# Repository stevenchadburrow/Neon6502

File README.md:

# Neon6502

<b>Compact 6502 build using 74' logic chips.</b>

The idea with this project is to make a cheap 4" x 4" PCB that can fit most of the functionality of my original <a href="https://github.com/stevenchadburrow/AcolyteComputer">Acolyte Computer</a>.  The purpose is to play games such as Tetris and Space Invaders clones that I will program in 6502 assembly.  I also made a simulator program is to help speed up development time and lessen the amount of Flash ROM burns.<br>

I'm doing this in order to wait for the <a href="https://www.microchip.com/en-us/product/PIC32CZ8110CA80144">PIC32CZ8110CA80144</a> microcontroller to come out in the LQFP-144 package (promised Q4 of 2025!).  Once that is out, I will get back to projects similar to my <a href="https://github.com/stevenchadburrow/AcolyteHandheld">Acolyte Handheld<a>.<br>

<b>Specs:</b><br>
- W65C02 running at 3.14 MHz<br>
- 32 KB of RAM (30 KB of which is Video RAM)<br>
- 32 KB of ROM (4x switchable banks)<br>
- 8x Built-in Buttons<br>
- VGA Output of 320x240 in 4-colors<br>
- Uses only 74' logic chips and the Flash ROM to generate the video signal!<br>
- USB-B to power device<br>
- No VIA, no UART, no keyboard, no audio, no external memory<br>

<b>Memory Map:</b><br>
- $0000 - $07FF = RAM<br>
- $0800 - $7FFF = Video RAM<br>
- $8000 - $FFFF = ROM<br>

<b>History:</b><br>
As this is a revisiting of previous projects and skills, I feel the need to try to catalog my progress up to this point.  Below is a timeline of projects completed with a few details.<br>
- Aug 2021: After the quarantine, I went back to work at the school physically.  I never went upstairs into my office but stayed in my classroom with a Linux computer to occupy my time.  I started researching how to make a water-based calculator, but found electricity to be far better.  I researched about 74' logic chips and eventually reached out to Garth who redirected me to the 6502.org Forum <a href="http://forum.6502.org/">here</a>.
- Oct 2021: This marks the very beginning of the journey, my first 6502 build, called "V1" by Bill (plasmo).  Made on perf-board, each wire hand-soldered.  I had crossed A4 and A11 on the RAM, Bill found this and fixed it for me.  It had only a couple of buttons and a 16x2 LCD.
- Nov 2021: I made a duplicate of V1 on a PCB, which I called "V2".  No bodges were required, though it wasn't very useful.  Far later I would use this as the basis for a project where Elizabeth soldered her own computer together.
- Jan 2022: I made V3 and even a V4, adding features such as PS/2 keyboard and ROM banks.  I tried to add VGA video using 74' logic chips for all sync calculations, but they were all failures.
- Mar 2022: In order to create a VGA video signal, I created my "Half a Pi" board, using a dedicated Flash ROM for video signals.  It was able to output White, Red, Cyan, and Black.  I was able to showcase it at the upcoming Math Appreciation Day 2022 <a href="http://forum.6502.org/viewtopic.php?f=1&t=7092">here</a>.
- Jul 2022: By now I had tried to replicate the "Half a Pi" with more complexity, and yet I continued to have failures.  At some point I had started calling them "Acolyte", though apparently the first versions were not operational.  The main goal was to combine both the sync signals and the program code onto a single Flash ROM.  Some were successes, even if they were complex, found <a href="http://forum.6502.org/viewtopic.php?f=4&t=7154">here</a>.
- Nov 2022: At this point I was still making mistakes and a lot of my PCBs would not work.  A revelation came to be at some point here that I could simply bodge wires to fix problems, which helped a lot.  You can find a lot of the discussion <a href="http://forum.6502.org/viewtopic.php?f=4&t=7407">here</a>.
- Jan 2023: The final culmination of the original Acolyte computers comes together <a href="https://github.com/stevenchadburrow/AcolyteComputer">here</a>.  It was named "Last Acolyte II".  It has so many bodge wires, mostly for experimenting and adding a VIA into the expansion area.  The back of that board looks like spagetti with all of the bodges!  It had Tetris, Space Invaders, BASIC, and a Monitor program.
- Apr 2023: I started designing the "Serial VGA" projects <a href="https://github.com/stevenchadburrow/SerialVGA">here</a>, which could be connected to any random 6502 computer.  After some revisions they started to work, but were not very efficient, being too slow.  I also played around with the Arduino, and created a CPLD-based shield <a href="https://github.com/stevenchadburrow/ArduinoShield">here</a>.
- Sep 2023: By now I had been working with CPLDs and learning Verilog, and created what I called "New Acolyte" <a href="https://github.com/stevenchadburrow/NewAcolyte">here</a>, which ran twice as fast and relied on the CPLD for video generation with 16 colors.  I connected a Sega Genesis controller to it, and was able to create many fun games for it, including Tetris, Space Invaders, Missile Command, Rogue, and Galaga clones.
- Dec 2023: After other failed revisions, it was time to go bigger and better, and so I developed my 'masterpiece', the "Acolyte816" <a href="https://github.com/stevenchadburrow/Acolyte816">here</a>.  It used a 65816 processor, CPLD for video generation, and a PIC16 micrcontroller for bootloading.  It did work, but was so complex that it was very hard to develop for.  Because of that, not much time was spent on it.
- Feb 2024: Enticed by the PIC16 which Garth had introduced to me, I started work on a PIC18 microcontroller based computer called "Acolyte Hand PIC'd", found <a href="https://github.com/stevenchadburrow/AcolyteHandPICd">here</a>.  It was a separation from the 6502 based computers, finally breaking away and being able to use C programming.  It still using a CPLD and external RAM for video generation.  I was able to get Tetris to run on it.  I would try another PIC18 project later that failed to work because I made it too complex.
- May 2024: I created a PIC24 microcontroller based computer called "Acolyte Hand PIC'd 24" <a href="https://github.com/stevenchadburrow/AcolyteHandPICd24">here</a>.  I was final able to break away from using the CPLD and external RAM for video generation, still yielding 16 colors.  Small additions to test USB host and device capabilities were added.  Then during Summer 2024 I created a two-player Pokemon clone for this computer, pushing the PIC24 to the very limit.
- Oct 2024: I upgraded to the PIC32 microcontroller, creating a computer called the "Acolyte Hand PIC'd 32" with absolutely stunning results <a href="https://github.com/stevenchadburrow/AcolyteHandPICd32">here</a>.  I started running it at 200 MHz, displaying 256 colors.  I bodged in better audio capabilities using an R2R DAC and was able to play video/audio streams.
- Dec 2024: After trying to port an NES emulator to the PIC32 board, and failing to reach the needed speed, I found the Peanut-GB Emulator by Mahyar <a href="https://github.com/deltabeard/Peanut-GB">here</a>.  It ran Gameboy games at full speed.  I quickly made a second revision of the PIC32 board with 64K color capability and 2x 8-bit R2R DACs.
- Jan 2025: Wanting to create a handheld device of some kind, I created "Mon Catcher" using a PIC24 and a small LCD.  It was going to be a dedicated device that would act similar to Pokemon GO, using sensors to detect movement.  It worked, but the sensors were not great and I got bored of it quickly. ( No links provided. )
- Feb 2025: I started work on what would later be called "PICnes" <a href="https://github.com/stevenchadburrow/PICnes">here</a>.  By April 2025 it would have all of the popular NES mappers including MMC3.
- Jun 2025: My dream forever has been to have a 'switchable' platform, and so I finally created the "Acolyte Handheld" <a href="https://github.com/stevenchadburrow/AcolyteHandheld">here</a>.  Capable of switching between VGA and LCD outputs, and being overclocked to 300 MHz, it was able to run nearly all NES games at full speed.  Along with Peanut-GB, I added TotalSMS <a href="https://github.com/ITotalJustice/TotalSMS">here</a>, for Sega Master System and Game Gear games.  Over Summer 2025 it was finalized.
- Aug 2025: In an attempt to shrink the Acolyte Handheld down, I created what I called the "Second Handheld", which would be my 'masterpiece' with the PIC32.  Unfortunately, I was not able to overclock it to 300 MHz, and many of the complex features such as external Flash ROM I had added were not working.  It ultimately ended a failure, however beautiful it was.  It seems that my 'masterpieces' always end in failure? ( No links provided. )
- Sep 2025: Seeking to make the next project better than the PIC32, I started the "RPi02W-Emulators" project <a href="https://github.com/stevenchadburrow/RPi02W-Emulators">here</a>.  Using a Raspberry Pi Zero 2W, I was able to make it 'switchable' between and LCD screen and HDMI output.  Programming in Linux was very enjoyable, though ultimately this project also proved to be a failure.  It ran NES and GB games easily enough, but Gameboy Advance games were still too slow.  The screen would have a tearing effect and the audio was scratchy, mainly because I decided to user /dev/fb0 and /dev/dsp for all of my video and audio needs.  The Linux overhead just didn't make it work as well as I had wanted.  It does run Freedoom, but only on HDMI.
- Nov 2025: And here we are, creating "Neon6502".  There is my journey.

<b>Links:</b><br>
<a href="https://www.youtube.com/shorts/nDpJQxdZJzY">Youtube Short playing Tetra</a><br>

<b>Pictures:</b><br>
Pictures of the PCB design, some footprints too small. Gerber files included.<br>
<br>
Testing out the image converter, assembly code, and simulator.<br>
<br>
Soldered PCB with all components.  Only one bodge wire!<br>
<br>
Actual program on VGA monitor.<br>
<br>
Tetra is always the first game.<br>
<br>
Enclosure uses same color palette.<br>
<br>
Ports fit flush with enclosure.<br>
<br>

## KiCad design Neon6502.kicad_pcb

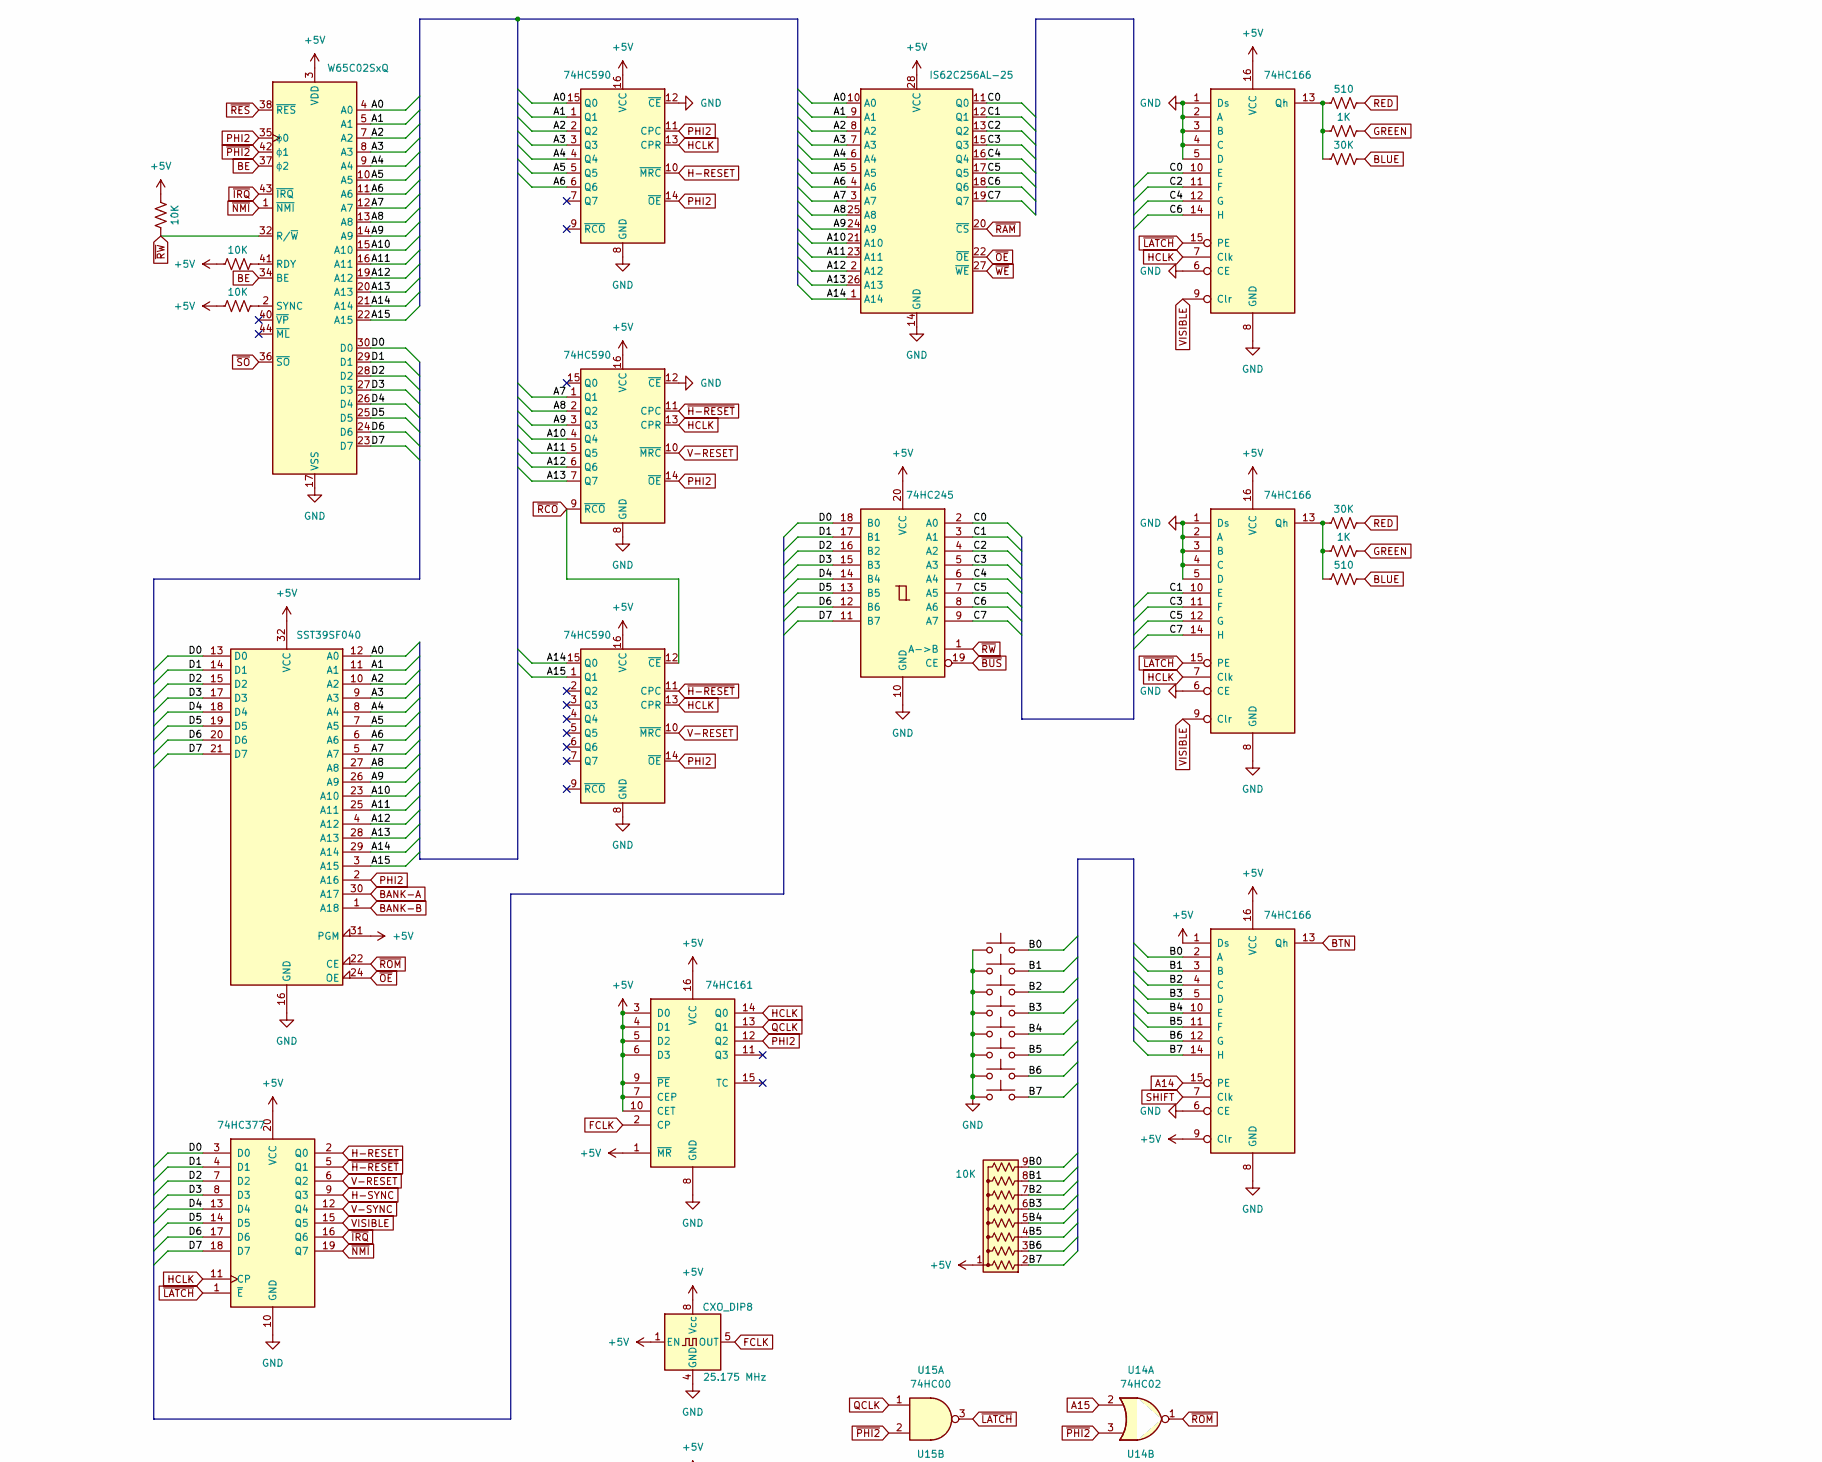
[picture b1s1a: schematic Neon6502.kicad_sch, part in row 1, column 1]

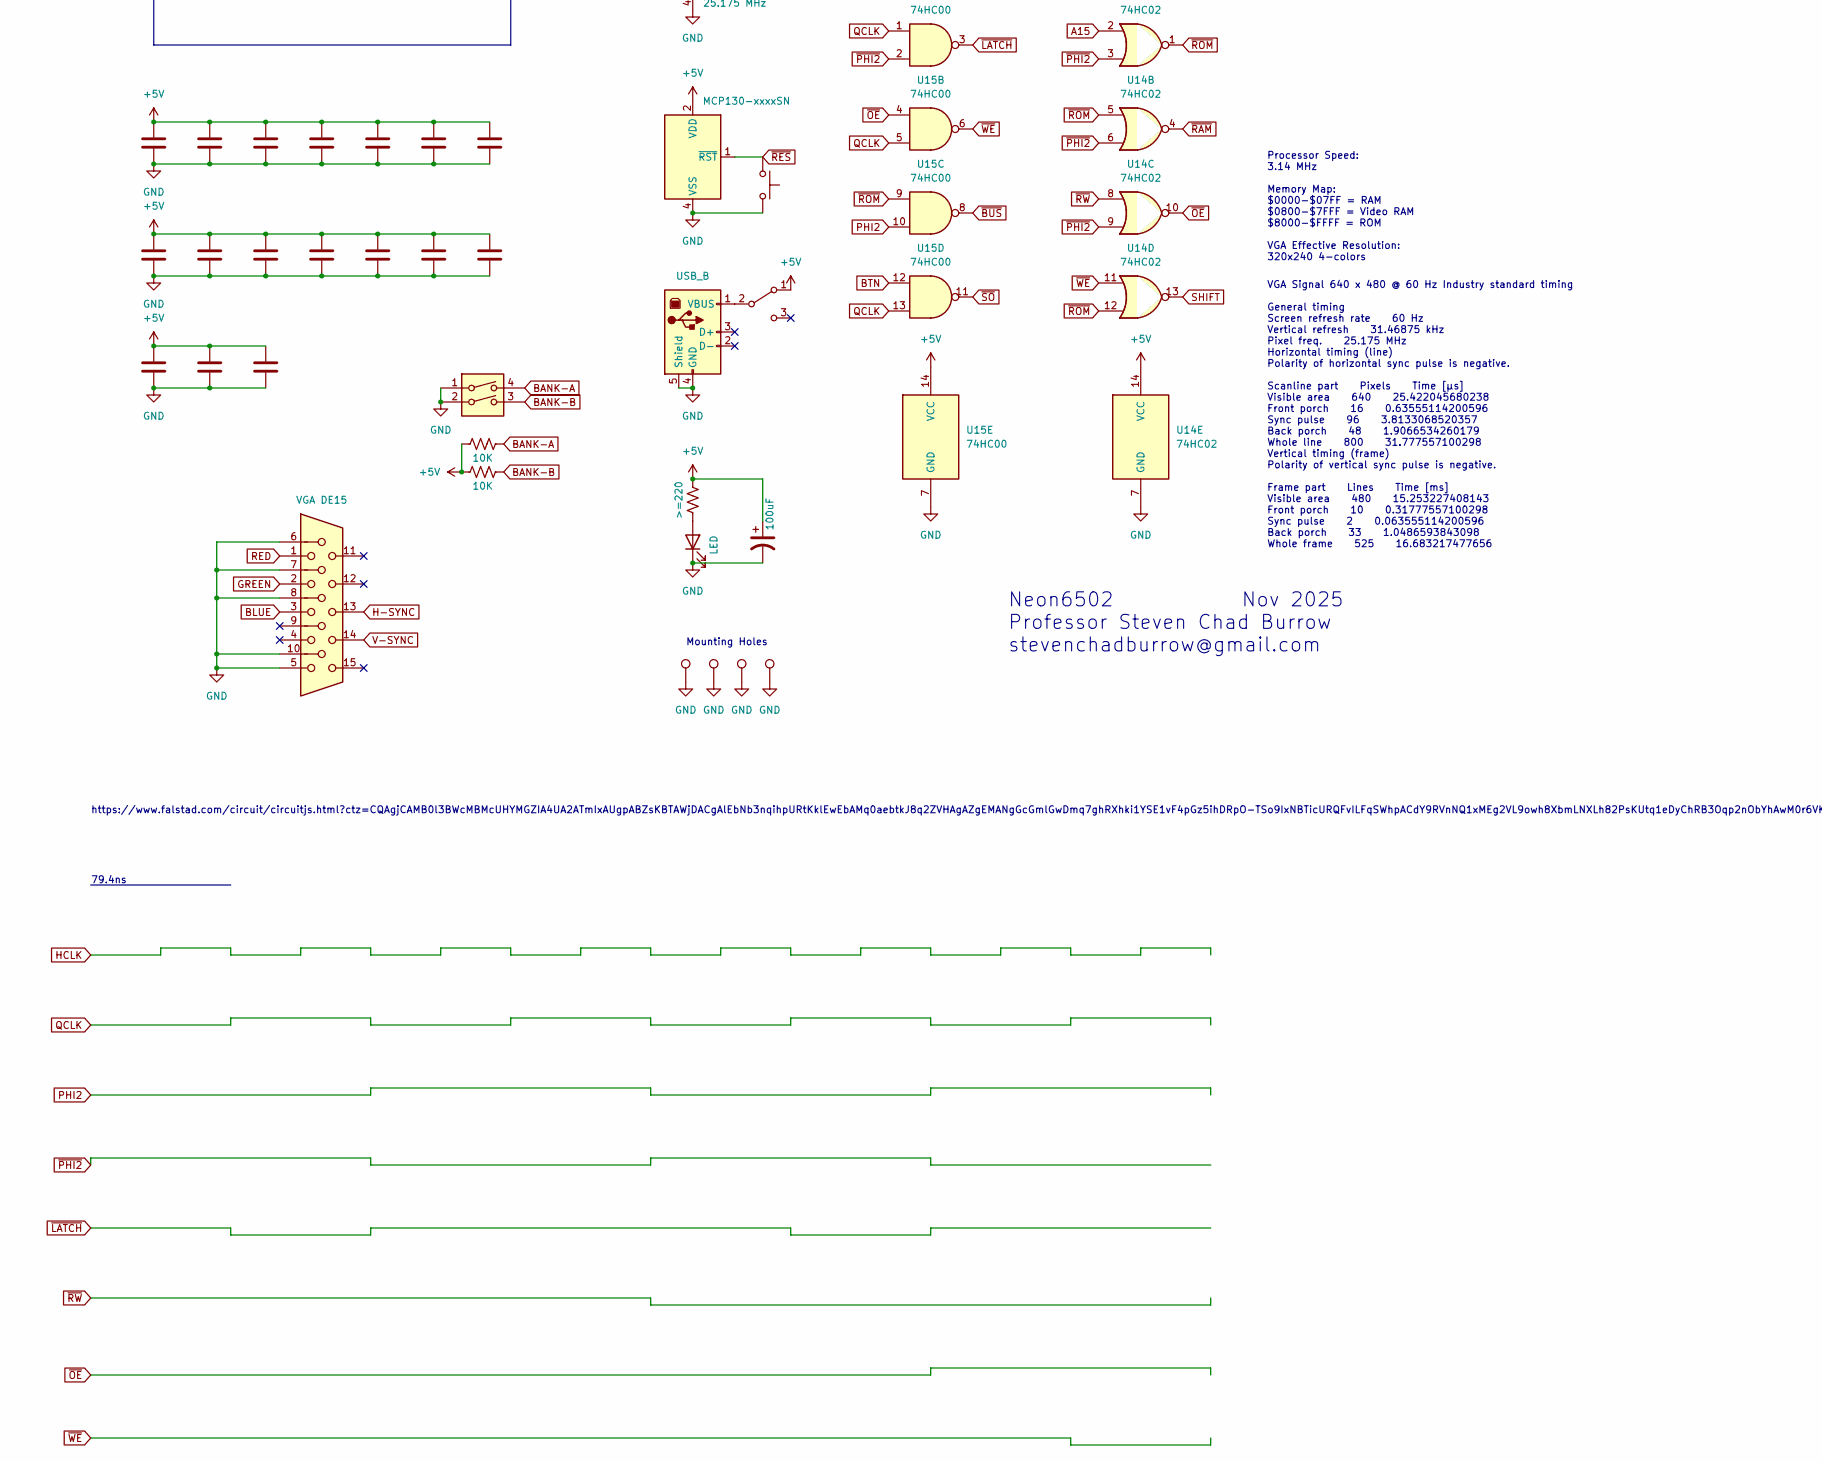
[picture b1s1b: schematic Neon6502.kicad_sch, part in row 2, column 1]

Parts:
C1: C_Polarized_US; CP_Radial_D6.3mm_P2.50mm
C2, C3, C4, C5, C6, C7, C8, C9, C10, C11, C12, C13, C14, C15, C16, C17, C18: C; C_1206_3216Metric_Pad1.33x1.80mm_HandSolder
D1: LED; CustomLED
J1: DE15_Receptacle_HighDensity; DSUB-15-HD_Female_Horizontal_P2.29x2.54mm_VGA
J2: USB_B; USB_B_Lumberg_2411_02_Horizontal
R1, R2, R3, R4, R5, R6, R7, R8, R9, R10, R11, R12: R_US; R_1206_3216Metric_Pad1.30x1.75mm_HandSolder
RN1: R_Network08_US; R_Array_SIP9
SW1, SW2, SW3, SW4, SW5, SW6, SW7, SW8: SW_Push; SW_PUSH_6mm_H5mm
SW9: SW_SPDT; SW_E-Switch_EG1224_SPDT_Angled
SW10: SW_Push; SW_Tactile_SPST_Angled_PTS645Vx83-2LFS
SW11: SW_DIP_x02; SW_DIP_SPSTx02_Slide_9.78x7.26mm_W7.62mm_P2.54mm
TP1, TP2, TP3, TP4: TestPoint; ScrewHole-4-40
U1: IS62C256AL-25; SOP-28_8.4x18.5mm_P1.27mm
U2, U3, U4: 74HC590; SO-16_3.9x9.9mm_P1.27mm
U5, U6, U12: 74HC166; SO-16_3.9x9.9mm_P1.27mm
U7: 74HC161; SO-16_3.9x9.9mm_P1.27mm
U8: MCP130-xxxxSN; SOIC-8_3.9x4.9mm_P1.27mm
U9: SST39SF040; DIP-32_W15.24mm_Socket
U10: 74HC377; SO-20_5.3x12.6mm_P1.27mm
U11: 74HC245; SO-20_5.3x12.6mm_P1.27mm
U13: W65C02SxQ; MQFP-44_10x10mm_P0.8mm
U14: 74HC02; SO-14_3.9x8.65mm_P1.27mm
U15: 74HC00; SO-14_3.9x8.65mm_P1.27mm
X2: CXO_DIP8; Oscillator_DIP-8

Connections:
+5V: C1.1, C2.1, C3.1, C4.1, C5.1, C6.1, C7.1, C8.1, C9.1, C10.1, C11.1, C12.1, C13.1, C14.1, C15.1, C16.1, C17.1, C18.1, R1.1, R2.1, R9.1, R10.1, R11.2, R12.1, RN1.1 (common), SW9.1 (A), U1.28 (VCC), U2.16 (VCC), U3.16 (VCC), U4.16 (VCC), U5.16 (VCC), U6.16 (VCC), U7.1 (~MR), U7.3 (D0), U7.4 (D1), U7.5 (D2), U7.6 (D3), U7.7 (CEP), U7.9 (~PE), U7.10 (CET), U7.16 (VCC), U8.2 (VDD), U9.31 (PGM), U9.32 (VCC), U10.20 (VCC), U11.20 (VCC), U12.1 (Ds), U12.9 (Clr), U12.16 (VCC), U13.3 (VDD), U13.31 (VDD), U14.14 (VCC), U15.14 (VCC), X2.1 (EN), X2.8 (Vcc)
/A0: U1.10 (A0), U2.15 (Q0), U9.12 (A0), U13.4 (A0)
/A1: U1.9 (A1), U2.1 (Q1), U9.11 (A1), U13.5 (A1)
/A2: U1.8 (A2), U2.2 (Q2), U9.10 (A2), U13.7 (A2)
/A3: U1.7 (A3), U2.3 (Q3), U9.9 (A3), U13.8 (A3)
/A4: U1.6 (A4), U2.4 (Q4), U9.8 (A4), U13.9 (A4)
/A5: U1.5 (A5), U2.5 (Q5), U9.7 (A5), U13.10 (A5)
/A6: U1.4 (A6), U2.6 (Q6), U9.6 (A6), U13.11 (A6)
/A7: U1.3 (A7), U3.1 (Q1), U9.5 (A7), U13.12 (A7)
/A8: U1.25 (A8), U3.2 (Q2), U9.27 (A8), U13.13 (A8)
/A9: U1.24 (A9), U3.3 (Q3), U9.26 (A9), U13.14 (A9)
/A10: U1.21 (A10), U3.4 (Q4), U9.23 (A10), U13.15 (A10)
/A11: U1.23 (A11), U3.5 (Q5), U9.25 (A11), U13.16 (A11)
/A12: U1.2 (A12), U3.6 (Q6), U9.4 (A12), U13.19 (A12)
/A13: U1.26 (A13), U3.7 (Q7), U9.28 (A13), U13.20 (A13)
/B0: RN1.9 (R8), SW1.2, U12.2 (A)
/B1: RN1.8 (R7), SW2.2, U12.3 (B)
/B2: RN1.7 (R6), SW3.2, U12.4 (C)
/B3: RN1.6 (R5), SW4.2, U12.5 (D)
/B4: RN1.5 (R4), SW5.2, U12.10 (E)
/B5: RN1.4 (R3), SW6.2, U12.11 (F)
/B6: RN1.3 (R2), SW7.2, U12.12 (G)
/B7: RN1.2 (R1), SW8.2, U12.14 (H)
/C0: U1.11 (Q0), U5.10 (E), U11.2 (A0)
/C1: U1.12 (Q1), U6.10 (E), U11.3 (A1)
/C2: U1.13 (Q2), U5.11 (F), U11.4 (A2)
/C3: U1.15 (Q3), U6.11 (F), U11.5 (A3)
/C4: U1.16 (Q4), U5.12 (G), U11.6 (A4)
/C5: U1.17 (Q5), U6.12 (G), U11.7 (A5)
/C6: U1.18 (Q6), U5.14 (H), U11.8 (A6)
/C7: U1.19 (Q7), U6.14 (H), U11.9 (A7)
/D0: U9.13 (D0), U10.3 (D0), U11.18 (B0), U13.30 (D0)
/D1: U9.14 (D1), U10.4 (D1), U11.17 (B1), U13.29 (D1)
/D2: U9.15 (D2), U10.7 (D2), U11.16 (B2), U13.28 (D2)
/D3: U9.17 (D3), U10.8 (D3), U11.15 (B3), U13.27 (D3)
/D4: U9.18 (D4), U10.13 (D4), U11.14 (B4), U13.26 (D4)
/D5: U9.19 (D5), U10.14 (D5), U11.13 (B5), U13.25 (D5)
/D6: U9.20 (D6), U10.17 (D6), U11.12 (B6), U13.24 (D6)
/D7: U9.21 (D7), U10.18 (D7), U11.11 (B7), U13.23 (D7)
A14: U1.1 (A14), U4.15 (Q0), U9.29 (A14), U12.15 (PE), U13.21 (A14)
A15: U4.1 (Q1), U9.3 (A15), U13.22 (A15), U14.2
BANK-A: R10.2, SW11.4, U9.30 (A17)
BANK-B: R12.2, SW11.3, U9.1 (A18)
BE: U13.34 (BE), U13.37 (ϕ2)
BLUE: J1.3, R5.2, R8.2
BTN: U12.13 (Qh), U15.12
FCLK: U7.2 (CP), X2.5 (OUT)
GND: C1.2, C2.2, C3.2, C4.2, C5.2, C6.2, C7.2, C8.2, C9.2, C10.2, C11.2, C12.2, C13.2, C14.2, C15.2, C16.2, C17.2, C18.2, D1.1 (K), J1.5, J1.6, J1.7, J1.8, J1.10, J2.4 (GND), J2.5 (Shield), SW1.1, SW2.1, SW3.1, SW4.1, SW5.1, SW6.1, SW7.1, SW8.1, SW10.2, SW11.1, SW11.2, TP1.1, TP2.1, TP3.1, TP4.1, U1.14 (GND), U2.8 (GND), U2.12 (~CE), U3.8 (GND), U3.12 (~CE), U4.8 (GND), U5.1 (Ds), U5.2 (A), U5.3 (B), U5.4 (C), U5.5 (D), U5.6 (CE), U5.8 (GND), U6.1 (Ds), U6.2 (A), U6.3 (B), U6.4 (C), U6.5 (D), U6.6 (CE), U6.8 (GND), U7.8 (GND), U8.4 (VSS), U9.16 (GND), U10.10 (GND), U11.10 (GND), U12.6 (CE), U12.8 (GND), U13.17 (VSS), U13.18 (VSS), U13.39 (VSS), U14.7 (GND), U15.7 (GND), X2.4 (GND)
GREEN: J1.2, R4.2, R7.2
H-RESET: U2.10 (~MRC), U10.2 (Q0)
H-SYNC: J1.13, U10.9 (Q3)
HCLK: U2.13 (CPR), U3.13 (CPR), U4.13 (CPR), U5.7 (Clk), U6.7 (Clk), U7.14 (Q0), U10.11 (CP)
unnamed: D1.2 (A), R11.1
unnamed: J2.1 (VBUS), SW9.2 (B)
unnamed: R3.1, R4.1, R5.1, U5.13 (Qh)
unnamed: R6.1, R7.1, R8.1, U6.13 (Qh)
unnamed: R2.2, U13.41 (RDY)
unnamed: R1.2, U13.2 (SYNC)
PHI2: U2.11 (CPC), U2.14 (~OE), U3.14 (~OE), U4.14 (~OE), U7.12 (Q2), U9.2 (A16), U13.35 (ϕ0), U15.10
QCLK: U7.13 (Q1), U15.1, U15.5, U15.13
RED: J1.1, R3.2, R6.2
SHIFT: U12.7 (Clk), U14.13
V-RESET: U3.10 (~MRC), U4.10 (~MRC), U10.6 (Q2)
V-SYNC: J1.14, U10.12 (Q4)
VISIBLE: U5.9 (Clr), U6.9 (Clr), U10.15 (Q5)
~BUS: U11.19 (CE), U15.8
~H-RESET: U3.11 (CPC), U4.11 (CPC), U10.5 (Q1)
~IRQ: U10.16 (Q6), U13.43 (~IRQ)
~LATCH: U5.15 (PE), U6.15 (PE), U10.1 (~E), U15.3
~NMI: U10.19 (Q7), U13.1 (~NMI)
~OE: U1.22 (~OE), U9.24 (OE), U14.10, U15.4
~PHI2: U13.42 (ϕ1), U14.3, U14.6, U14.9, U15.2
~RAM: U1.20 (~CS), U14.4
~RCO: U3.9 (~RCO), U4.12 (~CE)
~RES: SW10.1, U8.1 (~RST), U13.38 (~RES)
~ROM: U9.22 (CE), U14.1, U14.5, U14.12, U15.9
~RW: R9.2, U11.1 (A->B), U13.32 (R/~W), U14.8
~SO: U13.36 (~SO), U15.11
~WE: U1.27 (~WE), U14.11, U15.6

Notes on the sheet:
79.4ns
Mounting Holes
VGA Signal 640 x 480 @ 60 Hz Industry standard timing General timing Screen refresh rate 60 Hz Vertical refresh 31.46875 kHz Pixel freq. 25.175 MHz Horizontal timing (line) Polarity of horizontal sync pulse is negative. Scanline part Pixels Time [µs] Visible area 640 25.422045680238 Front porch 16 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
Neon6502 Nov 2025 Professor Steven Chad Burrow stevenchadburrow@gmail.com
Processor Speed: 3.14 MHz Memory Map: $0000-$07FF = RAM $0800-$7FFF = Video RAM $8000-$FFFF = ROM VGA Effective Resolution: 320x240 4-colors
https://www.falstad.com/circuit/circuitjs.html?ctz=CQAgjCAMB0l3BWcMBMcUHYMGZIA4UA2ATmIxAUgpABZsKBTAWjDACgAlEbNb3nqihpURtKklEwEbAMq0aebtkJ8q2ZVHAgAZgEMANgGcGmlGwDmq7ghRXhki1YSE1vF4pGz5ihDRpO-TSo9IxNBTicURQFvILFqSWhpACdY9RVnNQ1xMEg2VL9owh8XbmLNXLh82PsKUtq1eDyChRB3Oqp2nObYhAwM0r6VKkqewopAzIn-Rvg2AHc0j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

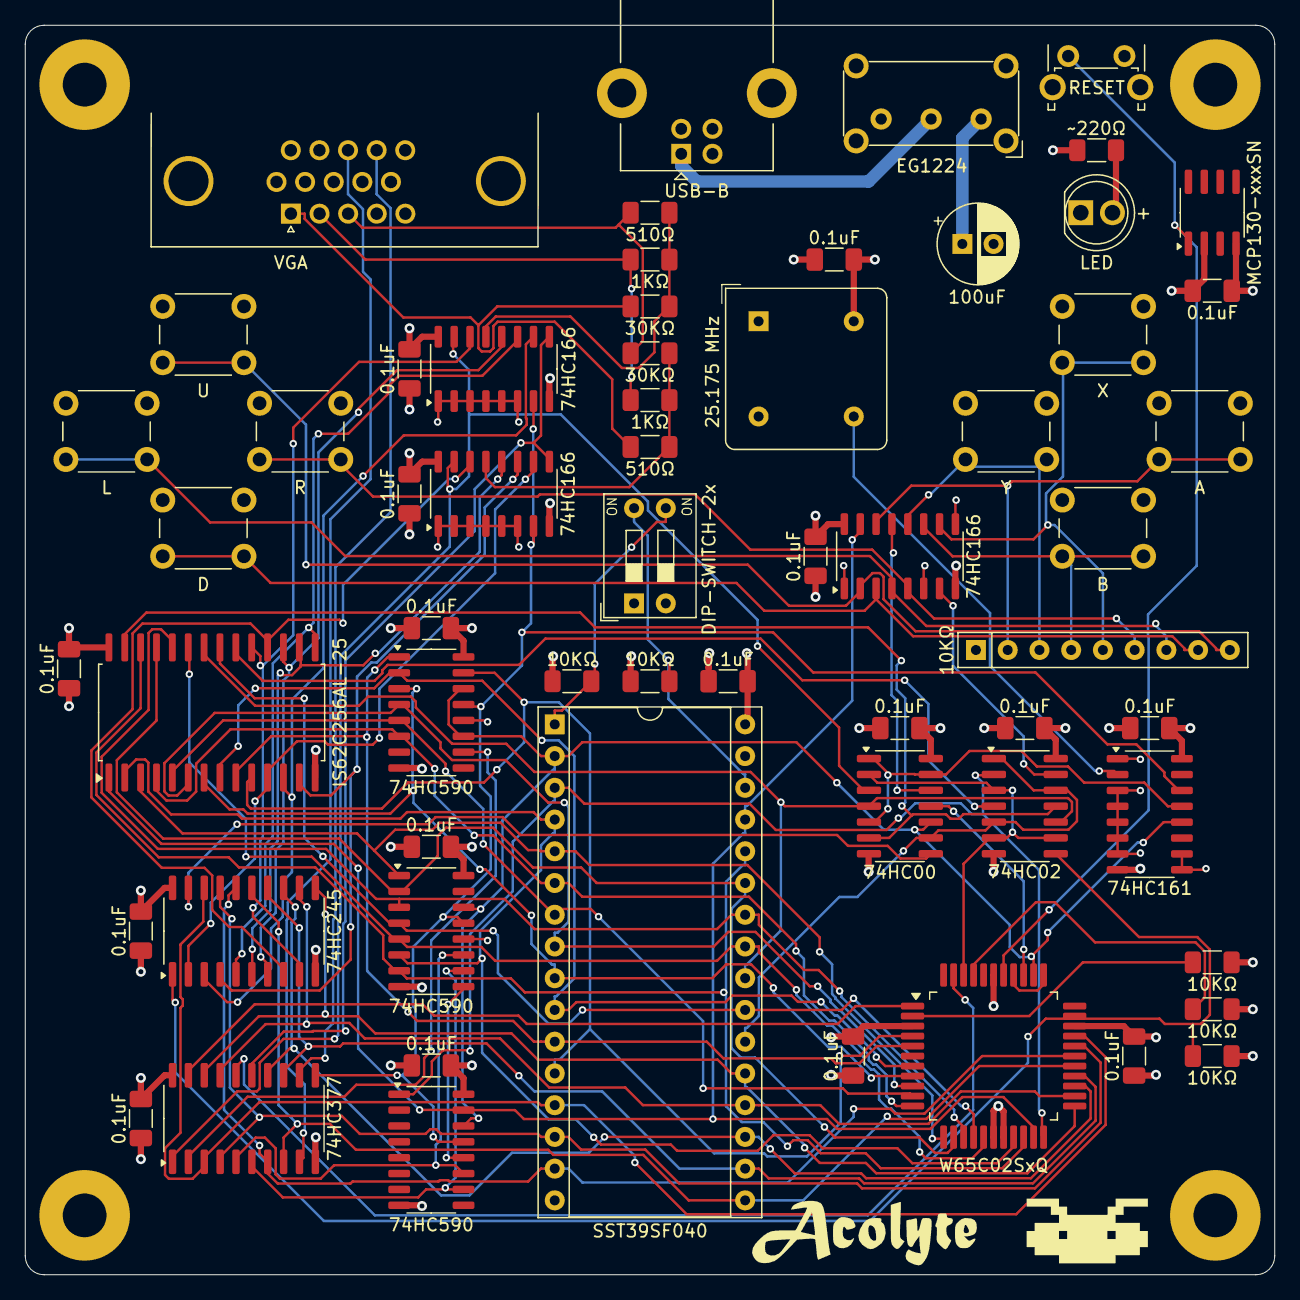
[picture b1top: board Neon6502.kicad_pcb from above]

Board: 4 copper layers, 100.0 x 100.0 mm, 67 parts (0 on the bottom side), 79 nets.

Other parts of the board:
G100: LOGO; AlienImage
G101: LOGO; AcolyteImage

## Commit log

2025-11-08 Rename Neo6502-Simulator.c to Neon6502-Simulator.c
2025-11-08 Rename Neo6502-Schematics.pdf to Neon6502-Schematics.pdf
2025-11-08 Rename Neo6502-Program.asm to Neon6502-Program.asm
2025-11-08 Rename Neo6502-PCB.png to Neon6502-PCB.png
2025-11-08 Rename Neo6502-Mandelbrot.png to Neon6502-Mandelbrot.png
2025-11-21 Rename Neon6502-Simulator.png to Neon6502-Simulated.png
